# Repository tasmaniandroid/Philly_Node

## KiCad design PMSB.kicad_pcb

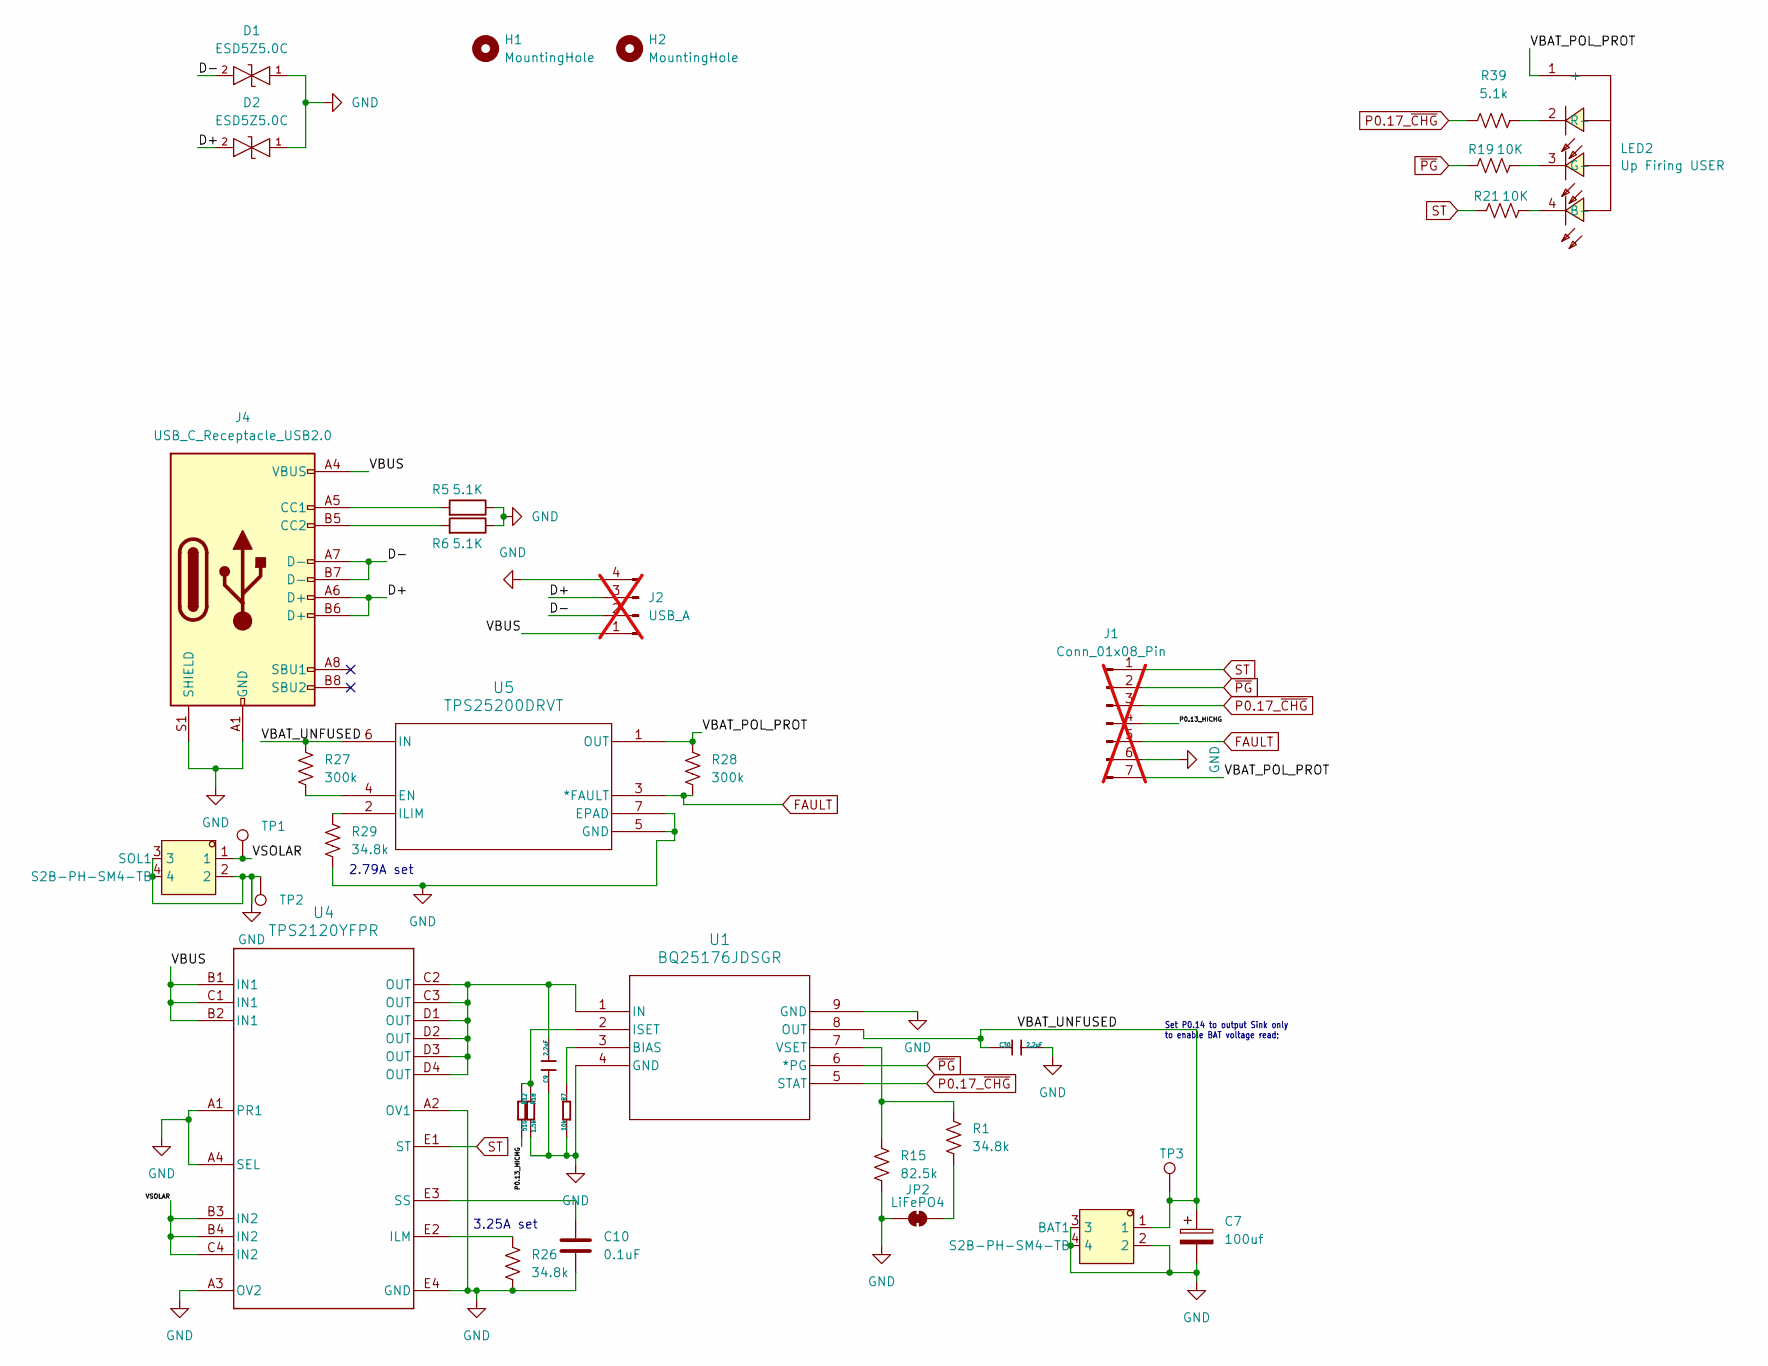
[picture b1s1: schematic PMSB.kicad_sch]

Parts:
BAT1: S2B-PH-SM4-TB; CONN-TH_S2B-PH-K-S-LF-SN
C7: 100uf; CP_Elec_5x4.5; LCSC C72473
C9, C30: 2.2uF; C_0402_1005Metric; LCSC C72203
C10: 0.1uF; C_0402_1005Metric
D1, D2: ESD5Z5.0C; SOD-523_L1.2-W0.8-LS1.6-BI
H1, H2: MountingHole; MountingHole_2.5mm
J1: Conn_01x08_Pin; PinHeader_1x08_P2.54mm_Vertical; not fitted
J2: USB_A; PinHeader_1x04_P2.54mm_Vertical; not fitted
J4: USB_C_Receptacle_USB2.0; USB_C_Receptacle_GCT_USB4110_MODIFIED_FOR_PROTRSION; LCSC C34260841
JP2: LiFePO4; SolderJumper
LED2: L201DS-QEPGBG2S; LCSC C404280
R1, R26, R29: 34.8k; R_0402_1005Metric; LCSC C47493
R5, R6: 5.1K; R_0402_1005Metric; LCSC C25905
R7: 10k; R_0402_1005Metric; LCSC C25744
R12: 510; R_0402_1005Metric; LCSC C25123
R15: 82.5k; R_0402_1005Metric; LCSC C11717
R18: 1.5k; R_0402_1005Metric; LCSC C25867
R19, R21: 10K; R_0402_1005Metric; LCSC C25744
R27, R28: 300k; R_0402_1005Metric; LCSC C270412
R39: 5.1k; R_0402_1005Metric; LCSC C25905
SOL1: S2B-PH-SM4-TB; CONN-TH_S2B-PH-K-S-LF-SN
TP1, TP2, TP3: TestPoint; TestPoint_Pad_1.0x1.0mm
U1: BQ25176JDSGR; WSON_MDSGR_TEX; LCSC C22407142
U4: TPS2120YFPR; YFP0020AAAA; LCSC C1850326
U5: TPS25200DRVT; DRV6_1X1P6_TEX; LCSC C128401

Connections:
/D+: D2.2, J2.3, J4.A6 (D+), J4.B6 (D+)
/D-: D1.2, J2.2, J4.A7 (D-), J4.B7 (D-)
/P0.13_HICHG: J1.4, R12.2
/VBAT_POL_PROT: J1.7, LED2.1 (+), R28.1, U5.1 (OUT)
/VBAT_UNFUSED: BAT1.1, C7.1, C30.1, R27.1, TP3.1, U1.8 (OUT), U5.6 (IN)
/VBUS: J2.1, J4.A4 (VBUS), J4.A9 (VBUS), J4.B4 (VBUS), J4.B9 (VBUS), U4.B1 (IN1), U4.B2 (IN1), U4.C1 (IN1)
/VSOLAR: SOL1.1, TP1.1, U4.B3 (IN2), U4.B4 (IN2), U4.C4 (IN2)
FAULT: J1.5, R28.2, U5.3 (*FAULT)
GND: BAT1.2, BAT1.3, BAT1.4, C7.2, C9.1, C10.2, C30.2, D1.1, D2.1, J1.6, J2.4, J4.A1 (GND), J4.A12 (GND), J4.B1 (GND), J4.B12 (GND), J4.S1 (SHIELD), JP2.1 (A), R5.1, R6.1, R7.2, R15.2, R18.2, R26.2, R29.2, SOL1.2, SOL1.3, SOL1.4, TP2.1, U1.4 (GND), U1.9 (GND), U4.A1 (PR1), U4.A2 (OV1), U4.A3 (OV2), U4.A4 (SEL), U4.E4 (GND), U5.5 (GND), U5.7 (EPAD)
unnamed: J4.A5 (CC1), R5.2
unnamed: J4.B5 (CC2), R6.2
unnamed: JP2.2 (B), R1.2
unnamed: LED2.4 (B-), R21.2
unnamed: LED2.3 (G-), R19.2
unnamed: LED2.2 (R-), R39.2
unnamed: R7.1, U1.3 (BIAS)
unnamed: C9.2, U1.1 (IN), U4.C2 (OUT), U4.C3 (OUT), U4.D1 (OUT), U4.D2 (OUT), U4.D3 (OUT), U4.D4 (OUT)
unnamed: R12.1, R18.1, U1.2 (ISET)
unnamed: R1.1, R15.1, U1.7 (VSET)
unnamed: R26.1, U4.E2 (ILM)
unnamed: C10.1, U4.E3 (SS)
unnamed: R27.2, U5.4 (EN)
unnamed: R29.1, U5.2 (ILIM)
P0.17_~CHG: J1.3, R39.1, U1.5 (STAT)
ST: J1.1, R21.1, U4.E1 (ST)
~PG: J1.2, R19.1, U1.6 (*PG)

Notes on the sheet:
2.79A set
3.25A set
Set P0.14 to output Sink only to enable BAT voltage read;

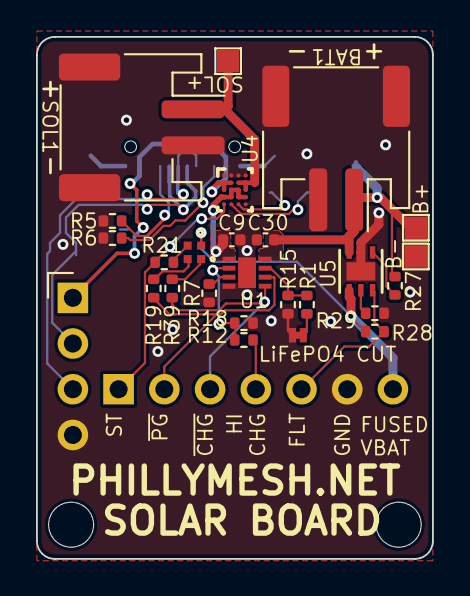
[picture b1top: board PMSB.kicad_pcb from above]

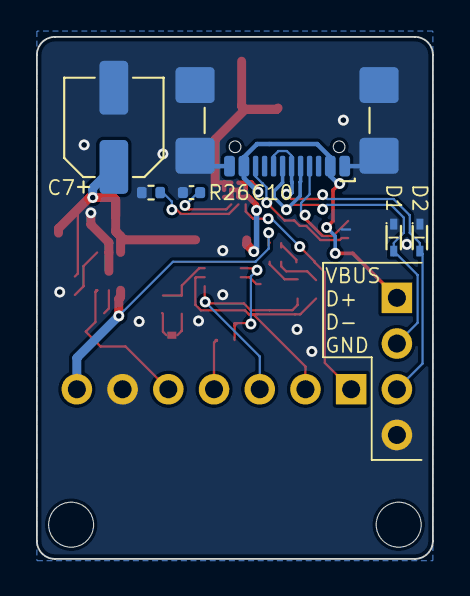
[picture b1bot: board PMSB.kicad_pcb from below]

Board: 2 copper layers, 22.0 x 29.0 mm, 35 parts (6 on the bottom side), 26 nets.

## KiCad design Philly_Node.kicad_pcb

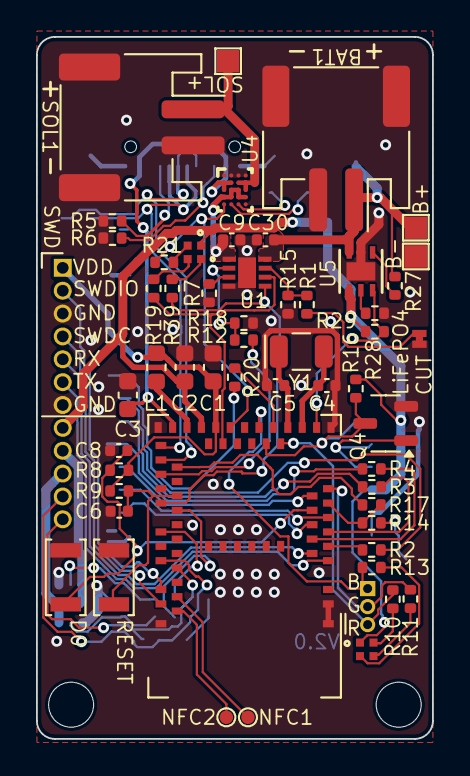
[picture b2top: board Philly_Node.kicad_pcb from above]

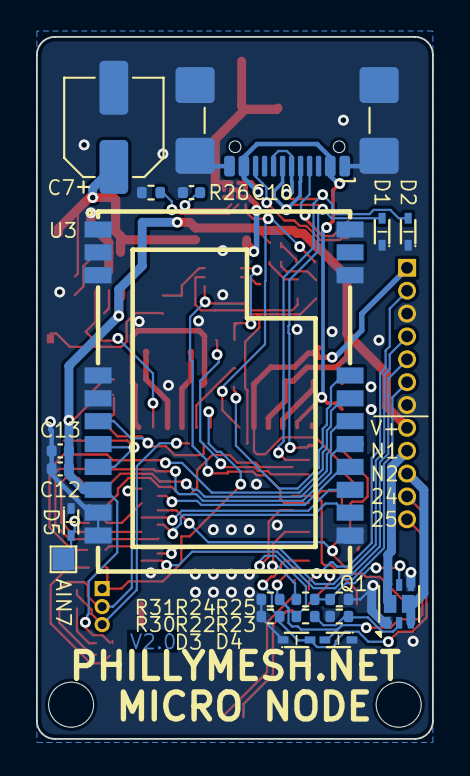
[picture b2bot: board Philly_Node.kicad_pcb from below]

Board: 2 copper layers, 22.0 x 39.0 mm, 77 parts (20 on the bottom side), 68 nets.

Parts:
BAT1: S2B-PH-SM4-TB; JST_PH_S2B-PH-SM4-TB_1x02-1MP_P2.00mm_Horizontal
C1, C2, C3: 4.7uF; C_0603_1608Metric
C4, C5: 12pF; C_0402_1005Metric
C6, C8, C10, C13: 0.1uF; C_0402_1005Metric
C7: 100uf; CP_Elec_5x4.5
C9, C30: 2.2uF; C_0402_1005Metric
C12: 10uF; C_0402_1005Metric
D1, D2, D3, D4, D5: LESD5D5_0CT1G; SOD-523_L1.2-W0.8-LS1.6-BI
H1, H2: MountingHole; MountingHole_2.5mm
J2: LED; PinSocket_1x03_P1.00mm_Vertical
J4: USB_C_Receptacle_USB2.0; USB_C_Receptacle_GCT_USB4110_MODIFIED_FOR_PROTRSION
J5: Multi; PinHeader_1x12_P1.27mm_Vertical
JP2: LiFePO4; SolderJumper
L1: 10uH; L_0603_1608Metric
LED1, LED2: L201DS-QEPGBG2S
NFC1, NFC2: TestPoint; TestPoint_Pad_D0.75mm
Q1: Q_Dual_NMOS_G1S2G2D2S1D1; DFN-6-1EP_2x2mm_P0.65mm_EP_DUAL
Q4: Q_NMOS_GSD; SOT-23-3
R1, R26, R29: 34.8k; R_0402_1005Metric
R2, R3, R4, R20, R22, R24: 22; R_0402_1005Metric
R5, R6: 5.1K; R_0402_1005Metric
R7, R8, R9: 10k; R_0402_1005Metric
R10, R13: 2.2K; R_0402_1005Metric
R11, R19, R21: 10K; R_0402_1005Metric
R12: 510; R_0402_1005Metric
R14, R23, R25: 1M; R_0402_1005Metric
R15: 82.5k; R_0402_1005Metric
R16: 100k; R_0402_1005Metric
R17: 510k; R_0402_1005Metric
R18: 1.5k; R_0402_1005Metric
R27, R28, R30, R31: 300k; R_0402_1005Metric
R39: 5.1k; R_0402_1005Metric
RESET1: RESET; SW_Tactile_SPST_NO_Straight_TVAF44-N015C-R
SOL1: S2B-PH-SM4-TB; JST_PH_S2B-PH-SM4-TB_1x02-1MP_P2.00mm_Horizontal
SW2: D0; SW_Tactile_SPST_NO_Straight_TVAF44-N015C-R
TP1, TP2, TP3, TP4: TestPoint; TestPoint_Pad_1.0x1.0mm
U1: BQ25176JDSGR; WSON_MDSGR_TEX
U2: MDBT50Q-U1MV2; Raytac_MDBT50Q
U3: E22-900M22S; WIRELM-SMD_E22-900M22S
U4: TPS2120YFPR; YFP0020AAAA
U5: TPS25200DRVT; DRV6_1X1P6_TEX
Y1: 32.768KHz; Crystal_SMD_MicroCrystal_CC7V-T1A-2Pin_3.2x1.5mm

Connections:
/D+: D2.2, J4.A6 (D+), J4.B6 (D+), U2.35 (D+)
/D-: D1.2, J4.A7 (D-), J4.B7 (D-), U2.34 (D-)
/DCCH: L1.2, U2.31 (DCCH)
/NFC+: NFC1.1, U2.52 (P0.09/NFC1)
/NFC-: NFC2.1, U2.54 (P0.10/NFC2)
/P0.13_HICHG: R12.2, U2.37 (P0.13)
/SWDCLK: J5.4, U2.53 (SWDCLK)
/SWDIO: J5.2, U2.51 (SWDIO)
/VBAT_POL_PROT: C2.2, C12.1, C13.1, J5.8, LED1.1 (+), LED2.1 (+), R16.1, R28.1, U2.30 (VDDH), U3.9 (VCC), U5.1 (OUT)
/VBAT_UNFUSED: BAT1.1, C7.1, C30.1, R27.1, TP3.1, U1.8 (OUT), U5.6 (IN)
/VBUS: C3.2, J4.A4 (VBUS), J4.A9 (VBUS), J4.B4 (VBUS), J4.B9 (VBUS), U2.32 (VBUS), U4.B1 (IN1), U4.B2 (IN1), U4.C1 (IN1)
/VDD: C1.2, J5.1, L1.1, R8.2, R9.2, U2.28 (VDD)
/VSOLAR: SOL1.1, TP1.1, U4.B3 (IN2), U4.B4 (IN2), U4.C4 (IN2)
AIN7: D5.2, R14.1, TP4.1
D0: C8.1, R8.1, SW2.1, U2.11 (P0.02/AIN0)
DIO2: Q4.1 (G), U3.7 (TXEN), U3.8 (DIO2)
GND: BAT1.2, BAT1.3, BAT1.4, C1.1, C2.1, C3.1, C4.2, C5.1, C6.2, C7.2, C8.2, C9.1, C10.2, C12.2, C13.2, C30.2, D1.1, D2.1, D3.1, D4.1, D5.1, J4.A1 (GND), J4.A12 (GND), J4.B1 (GND), J4.B12 (GND), J4.S1 (SHIELD), J5.3, J5.7, JP2.1 (A), Q1.1 (S), Q1.4 (S), Q4.2 (S), R5.1, R6.1, R7.2, R15.2, R18.2, R23.2, R25.2, R26.2, R29.2, R30.2, R31.2, RESET1.2, SOL1.2, SOL1.3, SOL1.4, SW2.2, TP2.1, U1.4 (GND), U1.9 (GND), U2.1 (GND), U2.2 (GND), U2.15 (GND), U2.33 (GND), U2.55 (GND), U3.1 (GND), U3.2 (GND), U3.3 (GND), U3.4 (GND), U3.5 (GND), U3.10 (GND), U3.11 (GND), U3.12 (GND), U3.20 (GND), U3.22 (GND), U4.A1 (PR1), U4.A2 (OV1), U4.A3 (OV2), U4.A4 (SEL), U4.E4 (GND), U5.5 (GND), U5.7 (EPAD)
LORA_BUSY: U2.10 (P0.29/AIN5), U3.14 (BUSY)
LORA_DIO1: U2.9 (P0.03/AIN1), U3.13 (DIO1)
LORA_MISO: R4.1, U2.7 (P1.14)
LORA_MOSI: R3.1, U2.8 (P1.15)
LORA_NRST: U2.13 (P0.28/AIN4), U3.15 (NRST)
LORA_NSS: R20.1, U2.20 (P0.04/AIN2)
LORA_SCK: R2.1, U2.6 (P1.13)
NMOS_1: J5.9, Q1.6 (D), Q1.7 (D)
NMOS_2: J5.10, Q1.3 (D), Q1.8 (D)
unnamed: J4.A5 (CC1), R5.2
unnamed: J4.B5 (CC2), R6.2
unnamed: JP2.2 (B), R1.2
unnamed: LED1.4 (B-), R13.2
unnamed: LED1.3 (G-), R11.2
unnamed: LED1.2 (R-), R10.2
unnamed: LED2.4 (B-), R21.2
unnamed: LED2.3 (G-), R19.2
unnamed: LED2.2 (R-), R39.2
unnamed: Q1.2 (G), R22.2, R23.1
unnamed: Q1.5 (G), R24.2, R25.1
unnamed: R7.1, U1.3 (BIAS)
unnamed: C9.2, U1.1 (IN), U4.C2 (OUT), U4.C3 (OUT), U4.D1 (OUT), U4.D2 (OUT), U4.D3 (OUT), U4.D4 (OUT)
unnamed: R12.1, R18.1, U1.2 (ISET)
unnamed: R1.1, R15.1, U1.7 (VSET)
unnamed: C4.1, U2.17 (XL1/P0.00), Y1.2
unnamed: C5.2, U2.18 (XL2/P0.01), Y1.1
unnamed: C6.1, R9.1, RESET1.1, U2.40 (~RESET/P0.18)
unnamed: R4.2, U3.16 (MISO)
unnamed: R3.2, U3.17 (MOSI)
unnamed: R20.2, U3.19 (NSS)
unnamed: R2.2, U3.18 (SCK)
unnamed: R26.1, U4.E2 (ILM)
unnamed: C10.1, U4.E3 (SS)
unnamed: R27.2, U5.4 (EN)
unnamed: R29.1, U5.2 (ILIM)
P0.06_USER_BLUE: J2.1, R13.1, U2.22 (P0.06)
P0.14_~READ_BAT: R17.2, U2.36 (P0.14)
P0.17_~CHG: R39.1, U1.5 (STAT), U2.41 (P0.17)
P0.19: R22.1, U2.42 (P0.19)
P0.20: R24.1, U2.44 (P0.20)
P0.24: D3.2, J5.11, R30.1, U2.48 (P0.24)
P0.25: D4.2, J5.12, R31.1, U2.49 (P0.25)
P0.26_USER_RED: J2.3, R10.1, U2.19 (P0.26)
P0.30_USER_GREEN: J2.2, R11.1, U2.14 (P0.30/AIN6)
P1.11_TX: J5.6, U2.4 (P1.11)
P1.12_RX: J5.5, U2.5 (P1.12)
RXEN: Q4.3 (D), R16.2, U2.21 (P0.05/AIN3), U3.6 (RXEN)
ST: R21.1, U2.26 (TRACEDATA3/P1.09), U4.E1 (ST)
VBAT_REF: R14.2, R17.1, U2.12 (P0.31/AIN7)
~FLT: R28.2, U2.16 (P0.27), U5.3 (*FAULT)
~PG: R19.1, U1.6 (*PG), U2.27 (TRACEDATA2/P0.11)

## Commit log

2026-01-28 Initial commit of nrf based micro node.
2026-02-10 Nearly done, final part number checks needed.
2026-02-12 Added D0 button, NFC pads, and library files.
2026-02-12 Update .gitignore to allow production files.
2026-02-12 Added courtyards, updated schematic to point to local lib footprints.
2026-02-14 changed to BQ25176JDSGR charge IC
2026-02-25 Changes to powerpath, added test points for battery/solar, misc other.
2026-03-17 Production order. Changed to Amphenol USB-C connector from clone.
2026-04-27 Adjustments to routing, added in more signals for solar input detection.
2026-04-29 Silkscreen and version number bump
2026-05-05 Add 2 user inputs with ESD diodes, break out old analog battery voltage monitor pin.
2026-06-22 Beginning of board adjustments to use multiple fabs.
2026-06-22 Start of PhillyMesh Solar Board
